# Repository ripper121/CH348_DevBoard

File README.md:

# CH348 DevBoard
### USB to Octal Serial / Uart ports

### Features:
- No drivers needed for Winows and Linux
- USB-C Connector
- USB ESD Protection
- 500mA Polyfuse (self resettable fuse)
- Leds:
 - RX shows data receiving status
 - TX shows data transmitting status
 - ACT shows USB configuration completed status
- Jumpers
 - CFG: During power-on, if the CFG pin is
at a high level or not connected, all DTRx/ TNOWx pins
are configured to function as TNOW. CFG pin is low, all
DTRx/ TNOWx pins are configured for DTR function.
- VIO: The power supply of RTS0, CTS0, DTR4, DTR5, DTR6 and DTR7 pins of CH348L come from VCC,
these pins are 3.3V signal level. The power supply of other UARTs and MODEM signal pins come
from VIO, which are 3.3V/2.5V/1.8V matching VIO signal level.
- JST PH 2.0mm 10 Pin Connectors for the UART Pins
 - 3V3, GND, RXD, TXD, RTS, CTS, DTR, DSR, DCD, RI
- Size 100 x 80 mm
- 3.2 mm mounting holes

###### From Datasheet:
- 480Mbps high-speed USB device interface, peripheral components only need crystal oscillator and capacitors
- Built-in firmware, emulate standard UART interface, used to upgrade the original serial peripheral or expand additional UART via USB
- Original serial applications are totally compatible without any modification in Windows operating systems
- Hardware full duplex UART interface, integrated independent transmit-receive buffer, supports communication baud rate varies from 1200bps to 6Mbps
- UART supports 8 data bits, supports odd, even, and none parity, supports 1 or 2 stop bits
- Integrated the 2048-byte RX FIFO and 1024-byte TX FIFO for each UART
- Supports common MODEM signals RTS, DTR, DCD, RI, DSR and CTS
- Supports CTS and RTS hardware automatic flow control
- Supports half-duplex, provides sending status TNOW, used for controlling RS485 to transmit-receive switch
- Supports up to 48-channel GPIO input and output function
- Supports RS232/RS485/RS422 interface, through external voltage conversion chip
- Built-in EEPROM used to configure the chip of VID, PID, maximum current value, vendor and product information string, etc

[CH348 Datasheet](https://github.com/ripper121/CH348_DevBoard/raw/main/Datasheets/CH348DS1.PDF "CH348 Datasheet")

[Driver & Software](http://www.wch-ic.com/search?q=CH348&t=downloads "Driver & Software")

If you want to order one assembled PCB: [Contact Me](https://ripper121.com/contact/ "Contact Me")

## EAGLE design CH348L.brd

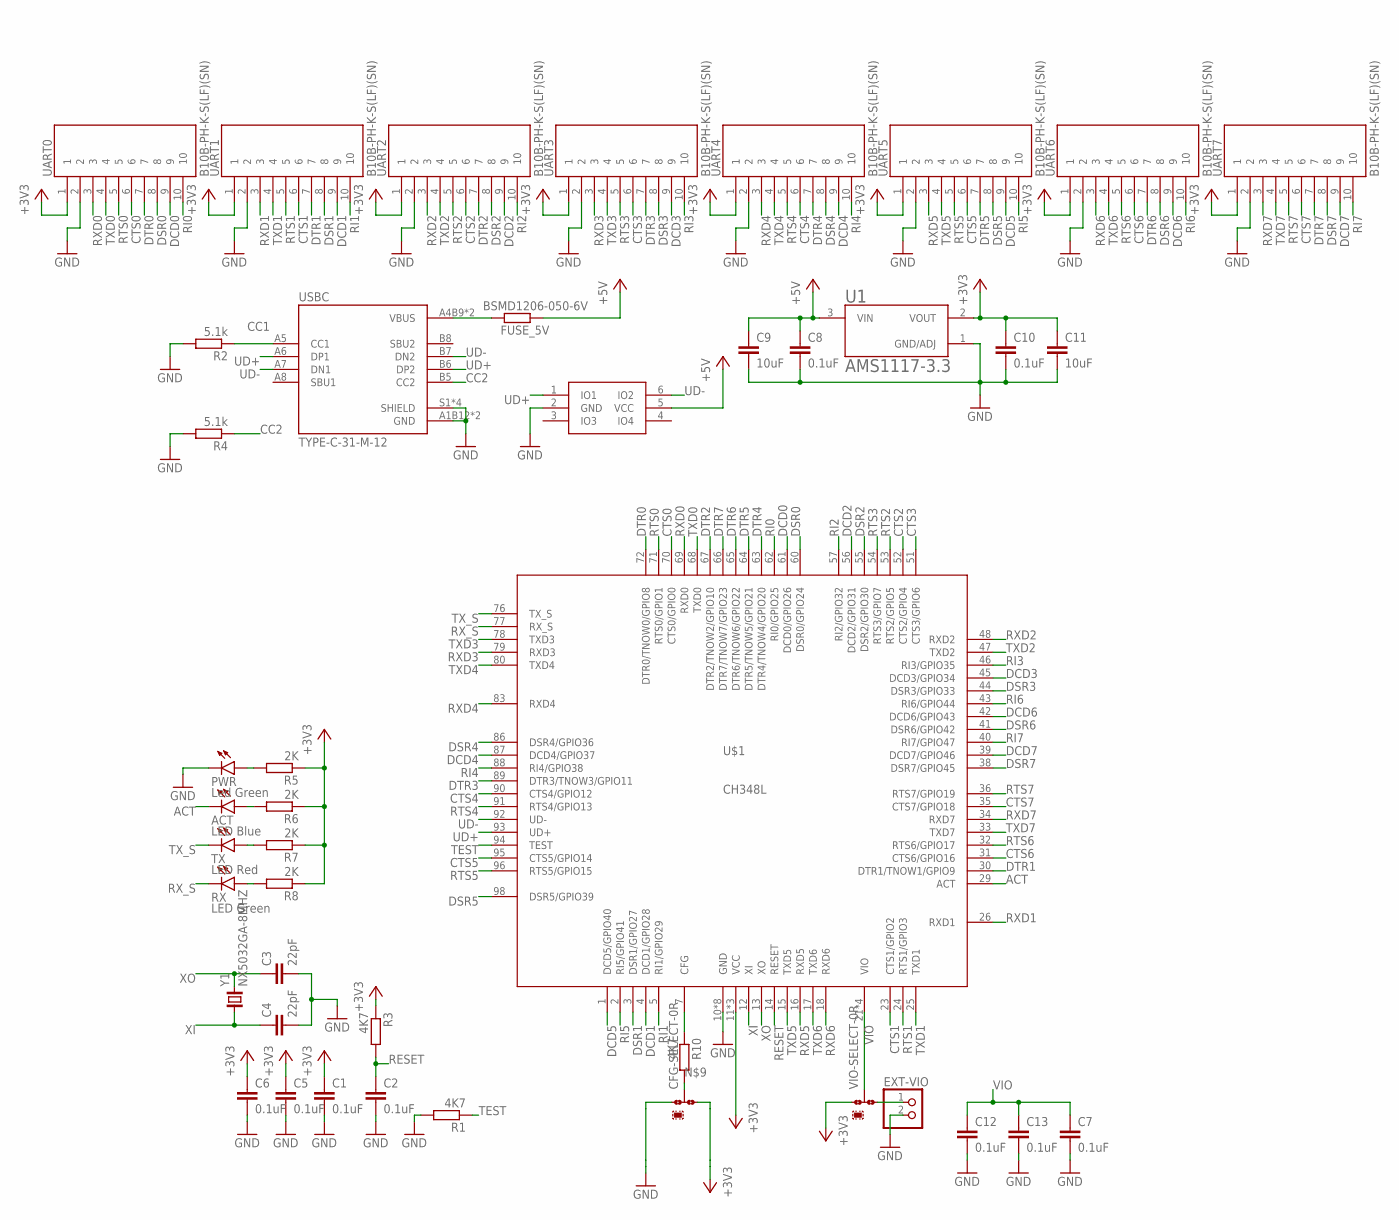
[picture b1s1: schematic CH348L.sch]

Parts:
ACT: LED Blue; CHIP-LED0603
C1, C2, C5, C6, C7, C8, C10, C12, C13: 0.1uF; C0603
C3, C4: 22pF; C0603
C9, C11: 10uF; C0805
CFG-SELECT: 0R-JUMPA; A0R-JMP
EXT-VIO: PINHD-1X2; 1X02
FUSE_5V: BSMD1206-050-6V; R1206
PWR: Led Green; CHIP-LED0603
R1, R3, R10: 4K7; R0603
R2, R4: 5.1k; R0603
R5, R6, R7, R8: 2K; R0603
RX: LED Green; CHIP-LED0603
TX: LED Red; CHIP-LED0603
U1: AMS1117-3.3; SOT229P700X180-4N
U5: ESDU5V0H4; SOT-23-6
U$1: CH348L; LQFP100_14X14
UART0, UART1, UART2, UART3, UART4, UART5, UART6, UART7: B10B-PH-K-S(LF)(SN); JST_S10B-PH-K-S(LF)(SN)
USBC: TYPE-C-31-M-12; HRO_TYPE-C-31-M-12
VIO-SELECT: 0R-JUMPA; A0R-JMP
Y1: NX5032GA-8MHZ; 2-SMD-5X3

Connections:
+3V3: C1.1, C5.1, C6.1, C10.1, C11.1, CFG-SELECT.3, R3.1, R5.1, R6.1, R7.1, R8.1, U1.2 (VOUT), U$1.11 (VCC), U$1.28 (VCC), U$1.75 (VCC), UART0.1, UART1.1, UART2.1, UART3.1, UART4.1, UART5.1, UART6.1, UART7.1, VIO-SELECT.1
+5V: C8.1, C9.1, FUSE_5V.1, U1.3 (VIN), U5.5 (VCC)
ACT: ACT.C, U$1.29 (ACT)
CC1: R2.1, USBC.A5 (CC1)
CC2: R4.1, USBC.B5 (CC2)
CFG: R10.1, U$1.7 (CFG)
CTS0: U$1.70 (CTS0/GPIO0), UART0.6
CTS1: U$1.23 (CTS1/GPIO2), UART1.6
CTS2: U$1.52 (CTS2/GPIO4), UART2.6
CTS3: U$1.51 (CTS3/GPIO6), UART3.6
CTS4: U$1.90 (CTS4/GPIO12), UART4.6
CTS5: U$1.95 (CTS5/GPIO14), UART5.6
CTS6: U$1.31 (CTS6/GPIO16), UART6.6
CTS7: U$1.35 (CTS7/GPIO18), UART7.6
DCD0: U$1.61 (DCD0/GPIO26), UART0.9
DCD1: U$1.4 (DCD1/GPIO28), UART1.9
DCD2: U$1.56 (DCD2/GPIO31), UART2.9
DCD3: U$1.45 (DCD3/GPIO34), UART3.9
DCD4: U$1.87 (DCD4/GPIO37), UART4.9
DCD5: U$1.1 (DCD5/GPIO40), UART5.9
DCD6: U$1.42 (DCD6/GPIO43), UART6.9
DCD7: U$1.39 (DCD7/GPIO46), UART7.9
DSR0: U$1.60 (DSR0/GPIO24), UART0.8
DSR1: U$1.3 (DSR1/GPIO27), UART1.8
DSR2: U$1.55 (DSR2/GPIO30), UART2.8
DSR3: U$1.44 (DSR3/GPIO33), UART3.8
DSR4: U$1.86 (DSR4/GPIO36), UART4.8
DSR5: U$1.98 (DSR5/GPIO39), UART5.8
DSR6: U$1.41 (DSR6/GPIO42), UART6.8
DSR7: U$1.38 (DSR7/GPIO45), UART7.8
DTR0: U$1.72 (DTR0/TNOW0/GPIO8), UART0.7
DTR1: U$1.30 (DTR1/TNOW1/GPIO9), UART1.7
DTR2: U$1.67 (DTR2/TNOW2/GPIO10), UART2.7
DTR3: U$1.89 (DTR3/TNOW3/GPIO11), UART3.7
DTR4: U$1.63 (DTR4/TNOW4/GPIO20), UART4.7
DTR5: U$1.64 (DTR5/TNOW5/GPIO21), UART5.7
DTR6: U$1.65 (DTR6/TNOW6/GPIO22), UART6.7
DTR7: U$1.66 (DTR7/TNOW7/GPIO23), UART7.7
GND: C1.2, C2.2, C3.2, C4.2, C5.2, C6.2, C7.2, C8.2, C9.2, C10.2, C11.2, C12.2, C13.2, CFG-SELECT.1, EXT-VIO.2, PWR.C, R1.2, R2.2, R4.2, U1.1 (GND/ADJ), U5.2 (GND), U$1.10 (GND), U$1.19 (GND), U$1.20 (GND), U$1.27 (GND), U$1.37 (GND), U$1.49 (GND), U$1.74 (GND), U$1.99 (GND), UART0.2, UART1.2, UART2.2, UART3.2, UART4.2, UART5.2, UART6.2, UART7.2, USBC.A1B12 (GND), USBC.B1A12 (GND), USBC.S1 (SHIELD), USBC.S2 (SHIELD), USBC.S3 (SHIELD), USBC.S4 (SHIELD)
unnamed: PWR.A, R5.2
unnamed: FUSE_5V.2, USBC.A4B9 (VBUS), USBC.B4A9 (VBUS)
unnamed: ACT.A, R6.2
unnamed: R7.2, TX.A
unnamed: R8.2, RX.A
unnamed: EXT-VIO.1, VIO-SELECT.3
unnamed: CFG-SELECT.2, R10.2
RESET: C2.1, R3.2, U$1.14 (RESET)
RI0: U$1.62 (RI0/GPIO25), UART0.10
RI1: U$1.5 (RI1/GPIO29), UART1.10
RI2: U$1.57 (RI2/GPIO32), UART2.10
RI3: U$1.46 (RI3/GPIO35), UART3.10
RI4: U$1.88 (RI4/GPIO38), UART4.10
RI5: U$1.2 (RI5/GPIO41), UART5.10
RI6: U$1.43 (RI6/GPIO44), UART6.10
RI7: U$1.40 (RI7/GPIO47), UART7.10
RTS0: U$1.71 (RTS0/GPIO1), UART0.5
RTS1: U$1.24 (RTS1/GPIO3), UART1.5
RTS2: U$1.53 (RTS2/GPIO5), UART2.5
RTS3: U$1.54 (RTS3/GPIO7), UART3.5
RTS4: U$1.91 (RTS4/GPIO13), UART4.5
RTS5: U$1.96 (RTS5/GPIO15), UART5.5
RTS6: U$1.32 (RTS6/GPIO17), UART6.5
RTS7: U$1.36 (RTS7/GPIO19), UART7.5
RXD0: U$1.69 (RXD0), UART0.3
RXD1: U$1.26 (RXD1), UART1.3
RXD2: U$1.48 (RXD2), UART2.3
RXD3: U$1.79 (RXD3), UART3.3
RXD4: U$1.83 (RXD4), UART4.3
RXD5: U$1.16 (RXD5), UART5.3
RXD6: U$1.18 (RXD6), UART6.3
RXD7: U$1.34 (RXD7), UART7.3
RX_S: RX.C, U$1.77 (RX_S)
TEST: R1.1, U$1.94 (TEST)
TXD0: U$1.68 (TXD0), UART0.4
TXD1: U$1.25 (TXD1), UART1.4
TXD2: U$1.47 (TXD2), UART2.4
TXD3: U$1.78 (TXD3), UART3.4
TXD4: U$1.80 (TXD4), UART4.4
TXD5: U$1.15 (TXD5), UART5.4
TXD6: U$1.17 (TXD6), UART6.4
TXD7: U$1.33 (TXD7), UART7.4
TX_S: TX.C, U$1.76 (TX_S)
UD+: U5.1 (IO1), U$1.93 (UD+), USBC.A6 (DP1), USBC.B6 (DP2)
UD-: U5.6 (IO2), U$1.92 (UD-), USBC.A7 (DN1), USBC.B7 (DN2)
VIO: C7.1, C12.1, C13.1, U$1.21 (VIO), U$1.22 (VIO), U$1.50 (VIO), U$1.100 (VIO), VIO-SELECT.2
XI: C4.1, U$1.12 (XI), Y1.1
XO: C3.1, U$1.13 (XO), Y1.2

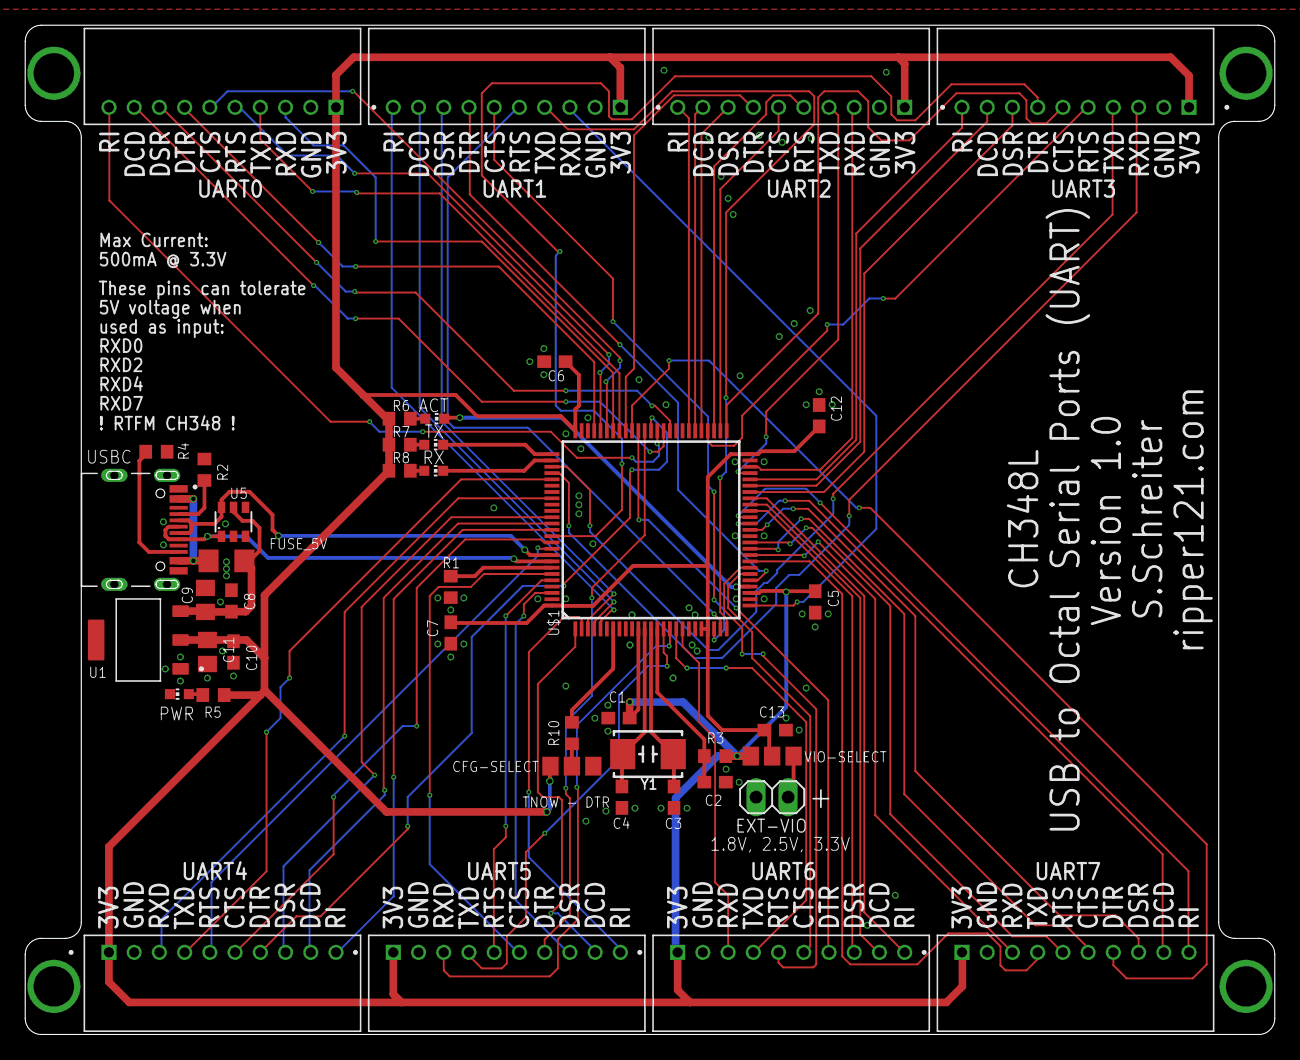
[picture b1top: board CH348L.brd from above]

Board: 2 copper layers, 99.1 x 80.0 mm, 43 parts (0 on the bottom side), 87 nets.

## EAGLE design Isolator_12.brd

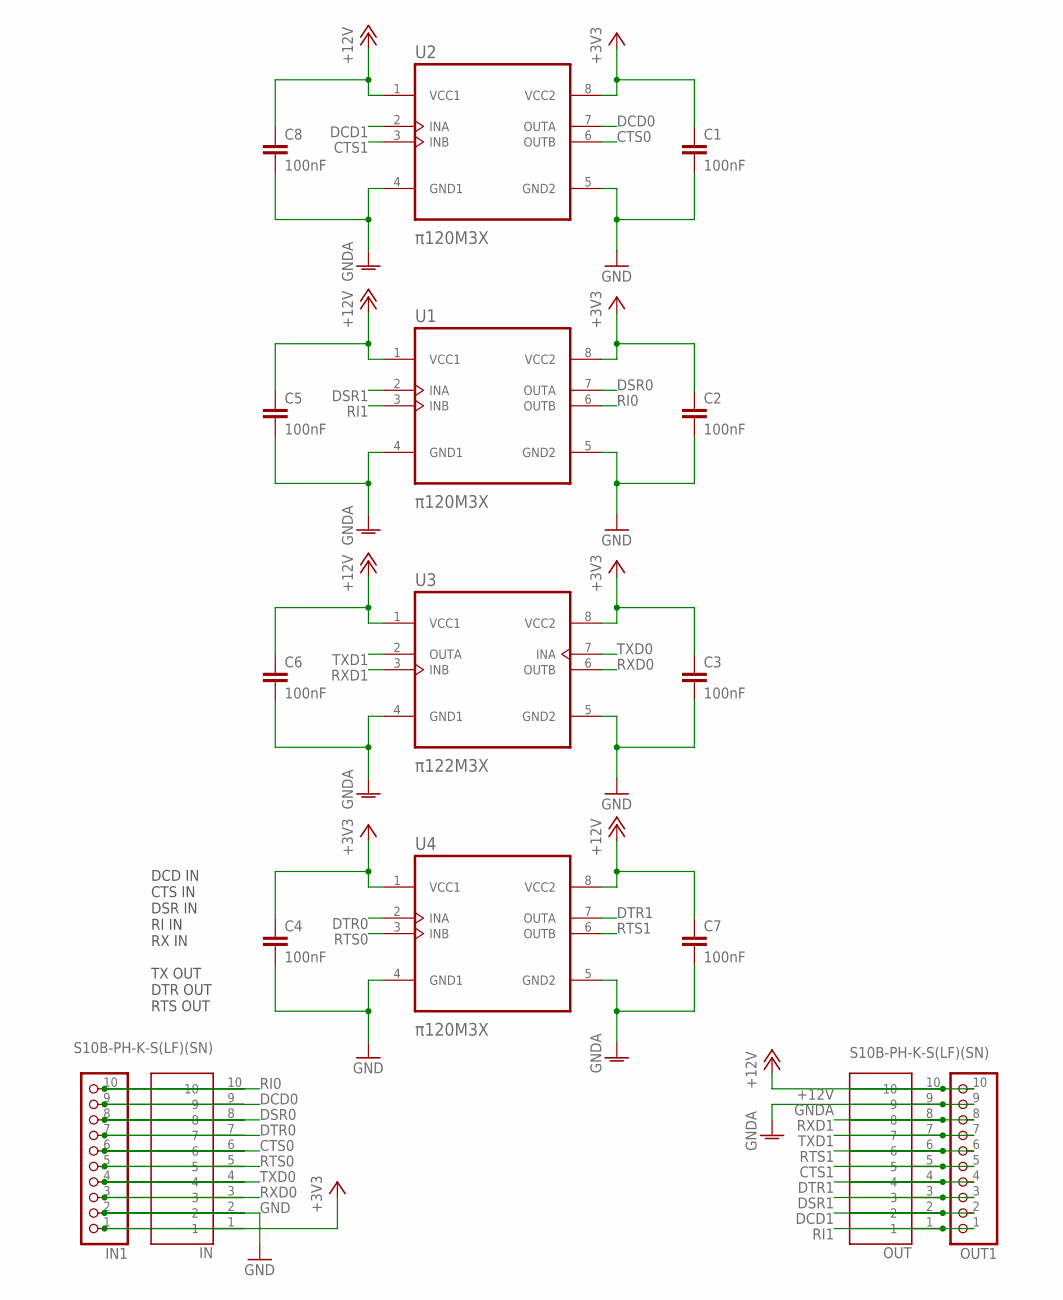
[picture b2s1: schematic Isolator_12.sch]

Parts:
C1, C2, C3, C4, C5, C6, C7, C8: 100nF; C0805
IN: S10B-PH-K-S(LF)(SN); JST_S10B-PH-K-S(LF)(SN)
IN1: PINHD-1X10; 1X10
OUT: S10B-PH-K-S(LF)(SN); JST_S10B-PH-K-S(LF)(SN)
OUT1: PINHD-1X10; 1X10
U1, U2, U4: π120M3X; SOIC-8
U3: π122M3X; SOIC-8

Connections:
+3V3: C1.1, C2.1, C3.1, C4.1, IN.1, IN1.1, U1.8 (VCC2), U2.8 (VCC2), U3.8 (VCC2), U4.1 (VCC1)
+12V: C5.1, C6.1, C7.1, C8.1, OUT.10, OUT1.10, U1.1 (VCC1), U2.1 (VCC1), U3.1 (VCC1), U4.8 (VCC2)
CTS0: IN.6, IN1.6, U2.6 (OUTB)
CTS1: OUT.5, OUT1.5, U2.3 (INB)
DCD0: IN.9, IN1.9, U2.7 (OUTA)
DCD1: OUT.2, OUT1.2, U2.2 (INA)
DSR0: IN.8, IN1.8, U1.7 (OUTA)
DSR1: OUT.3, OUT1.3, U1.2 (INA)
DTR0: IN.7, IN1.7, U4.2 (INA)
DTR1: OUT.4, OUT1.4, U4.7 (OUTA)
GND: C1.2, C2.2, C3.2, C4.2, IN.2, IN1.2, U1.5 (GND2), U2.5 (GND2), U3.5 (GND2), U4.4 (GND1)
GNDA: C5.2, C6.2, C7.2, C8.2, OUT.9, OUT1.9, U1.4 (GND1), U2.4 (GND1), U3.4 (GND1), U4.5 (GND2)
RI0: IN.10, IN1.10, U1.6 (OUTB)
RI1: OUT.1, OUT1.1, U1.3 (INB)
RTS0: IN.5, IN1.5, U4.3 (INB)
RTS1: OUT.6, OUT1.6, U4.6 (OUTB)
RXD0: IN.3, IN1.3, U3.6 (OUTB)
RXD1: OUT.8, OUT1.8, U3.3 (INB)
TXD0: IN.4, IN1.4, U3.7 (INA)
TXD1: OUT.7, OUT1.7, U3.2 (OUTA)

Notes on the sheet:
DCD IN CTS IN DSR IN RI IN RX IN TX OUT DTR OUT RTS OUT

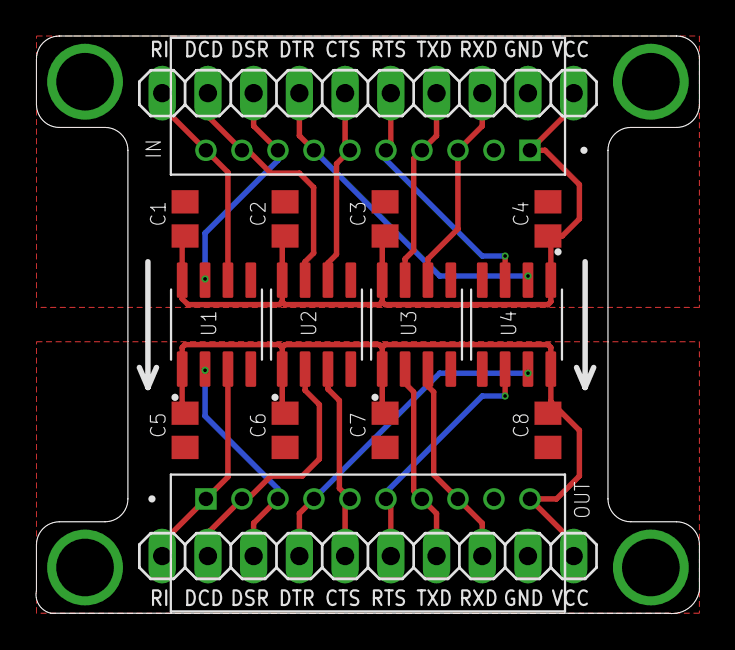
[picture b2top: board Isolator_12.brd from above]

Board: 2 copper layers, 36.9 x 32.1 mm, 16 parts (0 on the bottom side), 20 nets.

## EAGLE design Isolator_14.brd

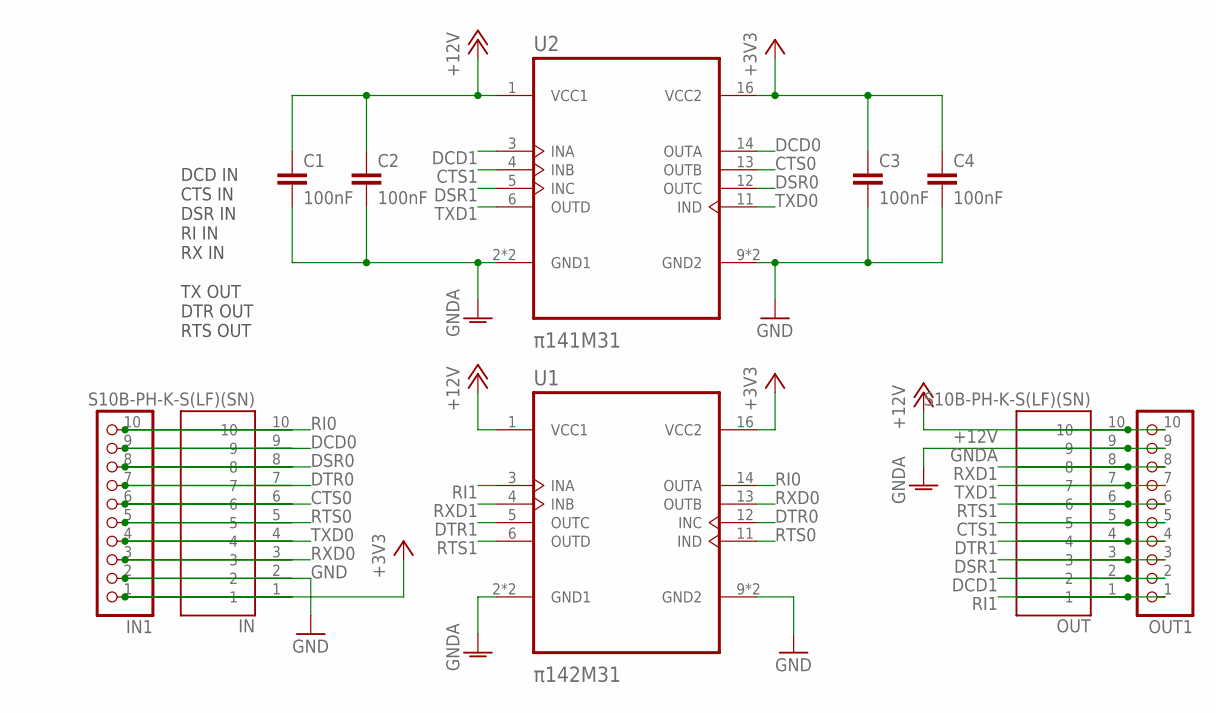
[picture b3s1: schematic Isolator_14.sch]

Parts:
C1, C2, C3, C4: 100nF; C0805
IN: S10B-PH-K-S(LF)(SN); JST_S10B-PH-K-S(LF)(SN)
IN1: PINHD-1X10; 1X10
OUT: S10B-PH-K-S(LF)(SN); JST_S10B-PH-K-S(LF)(SN)
OUT1: PINHD-1X10; 1X10
U1: π142M31; SOIC-16
U2: π141M31; SOIC-16

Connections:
+3V3: C3.1, C4.1, IN.1, IN1.1, U1.16 (VCC2), U2.16 (VCC2)
+12V: C1.1, C2.1, OUT.10, OUT1.10, U1.1 (VCC1), U2.1 (VCC1)
CTS0: IN.6, IN1.6, U2.13 (OUTB)
CTS1: OUT.5, OUT1.5, U2.4 (INB)
DCD0: IN.9, IN1.9, U2.14 (OUTA)
DCD1: OUT.2, OUT1.2, U2.3 (INA)
DSR0: IN.8, IN1.8, U2.12 (OUTC)
DSR1: OUT.3, OUT1.3, U2.5 (INC)
DTR0: IN.7, IN1.7, U1.12 (INC)
DTR1: OUT.4, OUT1.4, U1.5 (OUTC)
GND: C3.2, C4.2, IN.2, IN1.2, U1.9 (GND2), U1.15 (GND2), U2.9 (GND2), U2.15 (GND2)
GNDA: C1.2, C2.2, OUT.9, OUT1.9, U1.2 (GND1), U1.8 (GND1), U2.2 (GND1), U2.8 (GND1)
RI0: IN.10, IN1.10, U1.14 (OUTA)
RI1: OUT.1, OUT1.1, U1.3 (INA)
RTS0: IN.5, IN1.5, U1.11 (IND)
RTS1: OUT.6, OUT1.6, U1.6 (OUTD)
RXD0: IN.3, IN1.3, U1.13 (OUTB)
RXD1: OUT.8, OUT1.8, U1.4 (INB)
TXD0: IN.4, IN1.4, U2.11 (IND)
TXD1: OUT.7, OUT1.7, U2.6 (OUTD)

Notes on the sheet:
DCD IN CTS IN DSR IN RI IN RX IN TX OUT DTR OUT RTS OUT

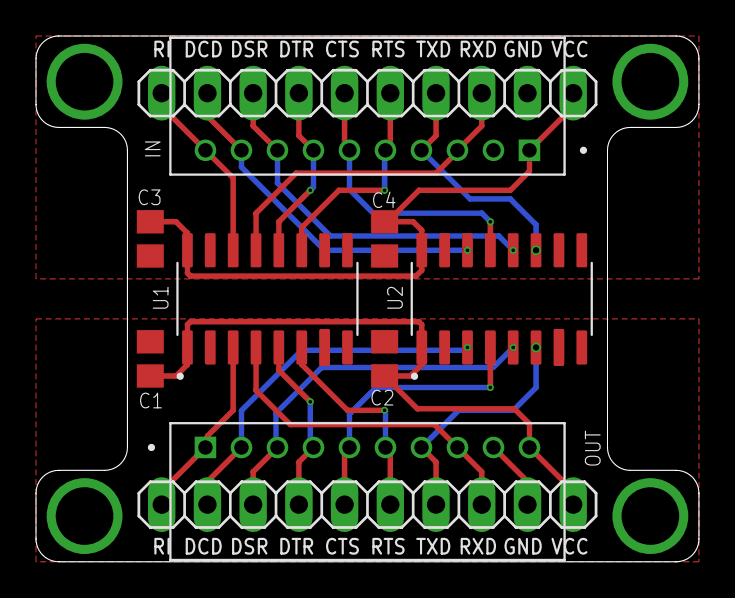
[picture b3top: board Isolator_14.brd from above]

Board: 2 copper layers, 36.8 x 29.2 mm, 10 parts (0 on the bottom side), 20 nets.

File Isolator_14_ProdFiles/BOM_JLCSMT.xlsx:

Comment | Designator | Footprint | JLCPCB Part #（optional）
100nF | C1, C2, C3, C4 | C0805
B10B-PH-K-S(LF)(SN) | IN | S10B-PH-K-S(LF)(SN)
π141M31 | U2 | SOIC-8
π142M31 | U1 | SOIC-8

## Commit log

2023-02-14 init
2023-02-14 images
2023-02-14 Isolator
2023-02-14 Rename
2023-02-18 GPIO Header, ESD
2023-03-10 Fixed UD+ UD- swap
2023-03-10 Driver & Tools
